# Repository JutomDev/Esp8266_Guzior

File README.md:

# Esp8266_Guzior
The project is a skill-based game using ESP8266 modules, where one master communicates wirelessly with multiple slaves via ESP-NOW. Each slave has a button and an LED, and players must press the button as quickly as possible when the LED lights up.

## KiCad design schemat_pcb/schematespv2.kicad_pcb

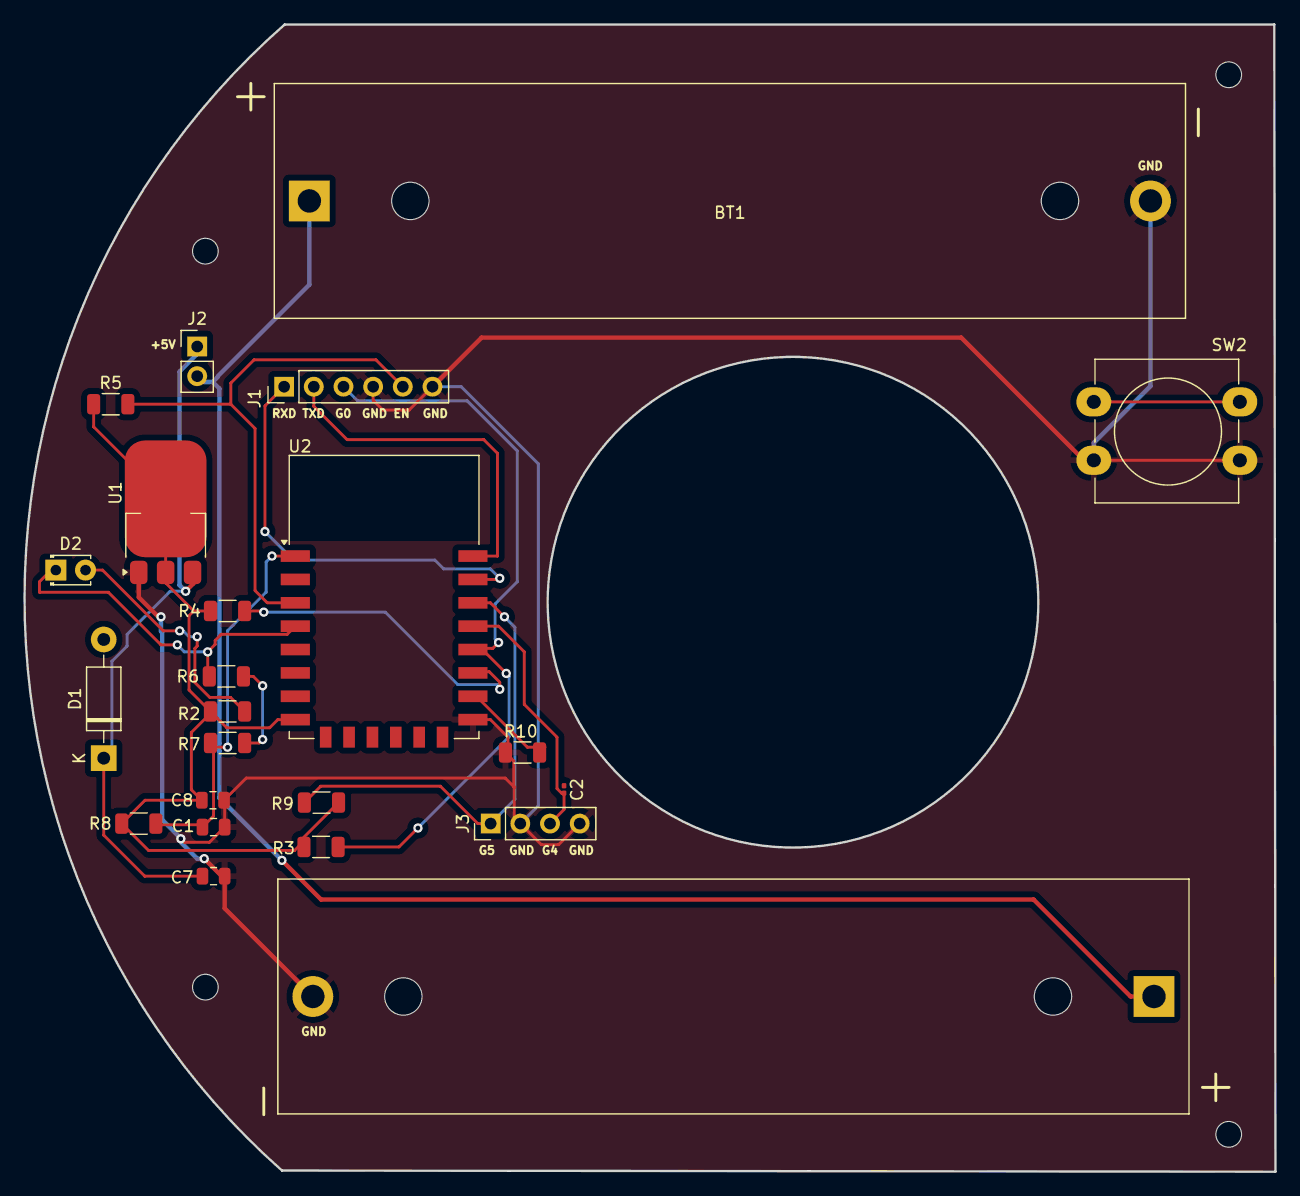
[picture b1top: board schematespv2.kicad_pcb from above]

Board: 4 copper layers, 107.1 x 98.2 mm, 27 parts (0 on the bottom side), 16 nets.

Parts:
BT1, BT2: Battery; BatteryHolder_MPD_BH-18650-PC2
C1: 100nF; C_0805_2012Metric
C2: 100nF; C_0201_0603Metric
C7, C8: 10uF; C_0805_2012Metric
D1: 1N5819; D_DO-41_SOD81_P10.16mm_Horizontal
D2: LED; LED_D1.8mm_W3.3mm_H2.4mm
J1: Conn_01x06_MountingPin; PinHeader_1x06_P2.54mm_Vertical
J2: Conn_01x02_MountingPin; PinHeader_1x02_P2.54mm_Vertical
J3: Conn_01x04_MountingPin; PinHeader_1x04_P2.54mm_Vertical
R2, R7, R9: 470; R_1206_3216Metric
R3, R4, R5, R8, R10: 12k; R_1206_3216Metric
R6: 0(NC); R_1206_3216Metric
SW2: SW_Push_Open; SW_PUSH-12mm_Wuerth-430476085716
U1: NCP1117ST33T3G; SOT-223-3_TabPin2
U2: ESP8266-12E_ESP-12E; ESP-12E
hole, hole1, hole2, hole3: MountingHole_2.2mm_M2

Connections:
/EN: J1.5, R5.2, U2.3 (EN)
/GPIO0: J1.3, R3.2, U2.18 (IO0)
/GPIO2: R4.2, U2.17 (IO2)
/GPIO4: C2.2, J3.3, U2.19 (IO4)
/GPIO5: J3.1, R9.1, U2.20 (IO5)
/GPIO15: R10.2, U2.16 (IO15)
/GPIO16: D2.1 (K), R6.1, U2.4 (IO16)
/RXD: J1.1, U2.21 (RXD)
/TXD: J1.2, U2.22 (TXD)
/nRST: C1.1, R7.1, R8.2, U2.1 (RESET)
GND: BT1.2 (-), BT2.2 (-), C1.2, C7.2, C8.2, J1.4, J1.6, J3.2, J3.4, R10.1, SW2.2 (B), U1.1 (GND), U2.15 (GND)
unnamed: BT1.1 (+), BT2.1 (+), J2.2
unnamed: D2.2 (A), R2.2
unnamed: R6.2, R7.2
VDD3V3: C8.1, R2.1, R3.1, R4.1, R5.1, R8.1, R9.2, U1.2 (OUT), U2.8 (VCC)
VDD5V: C7.1, D1.1 (K), J2.1, U1.3 (IN)

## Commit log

2025-07-16 Pierwszy commit projektu
2025-07-25 add test pcb
